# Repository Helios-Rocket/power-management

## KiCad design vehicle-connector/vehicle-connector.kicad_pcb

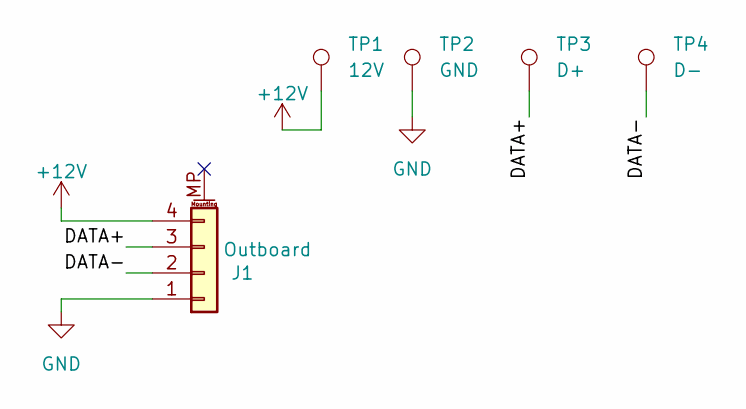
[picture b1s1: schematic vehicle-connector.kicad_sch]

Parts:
J1: Outboard; JST_ZE_SM04B-ZESS-TB_1x04-1MP_P1.50mm_Horizontal
TP1: 12V; TestPoint_Pad_4.0x4.0mm
TP2: GND; TestPoint_Pad_4.0x4.0mm
TP3: D+; TestPoint_Pad_4.0x4.0mm
TP4: D-; TestPoint_Pad_4.0x4.0mm

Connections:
+12V: J1.4, TP1.1 (1_1)
/DATA+: J1.3, TP3.1 (1_1)
/DATA-: J1.2, TP4.1 (1_1)
GND: J1.1, TP2.1 (1_1)

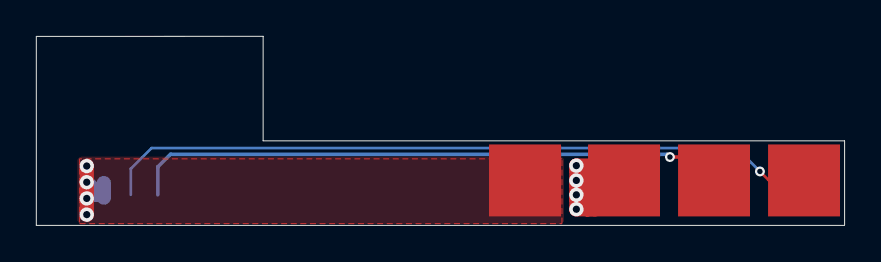
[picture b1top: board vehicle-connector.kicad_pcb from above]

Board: 2 copper layers, 44.9 x 10.5 mm, 5 parts (1 on the bottom side), 4 nets.

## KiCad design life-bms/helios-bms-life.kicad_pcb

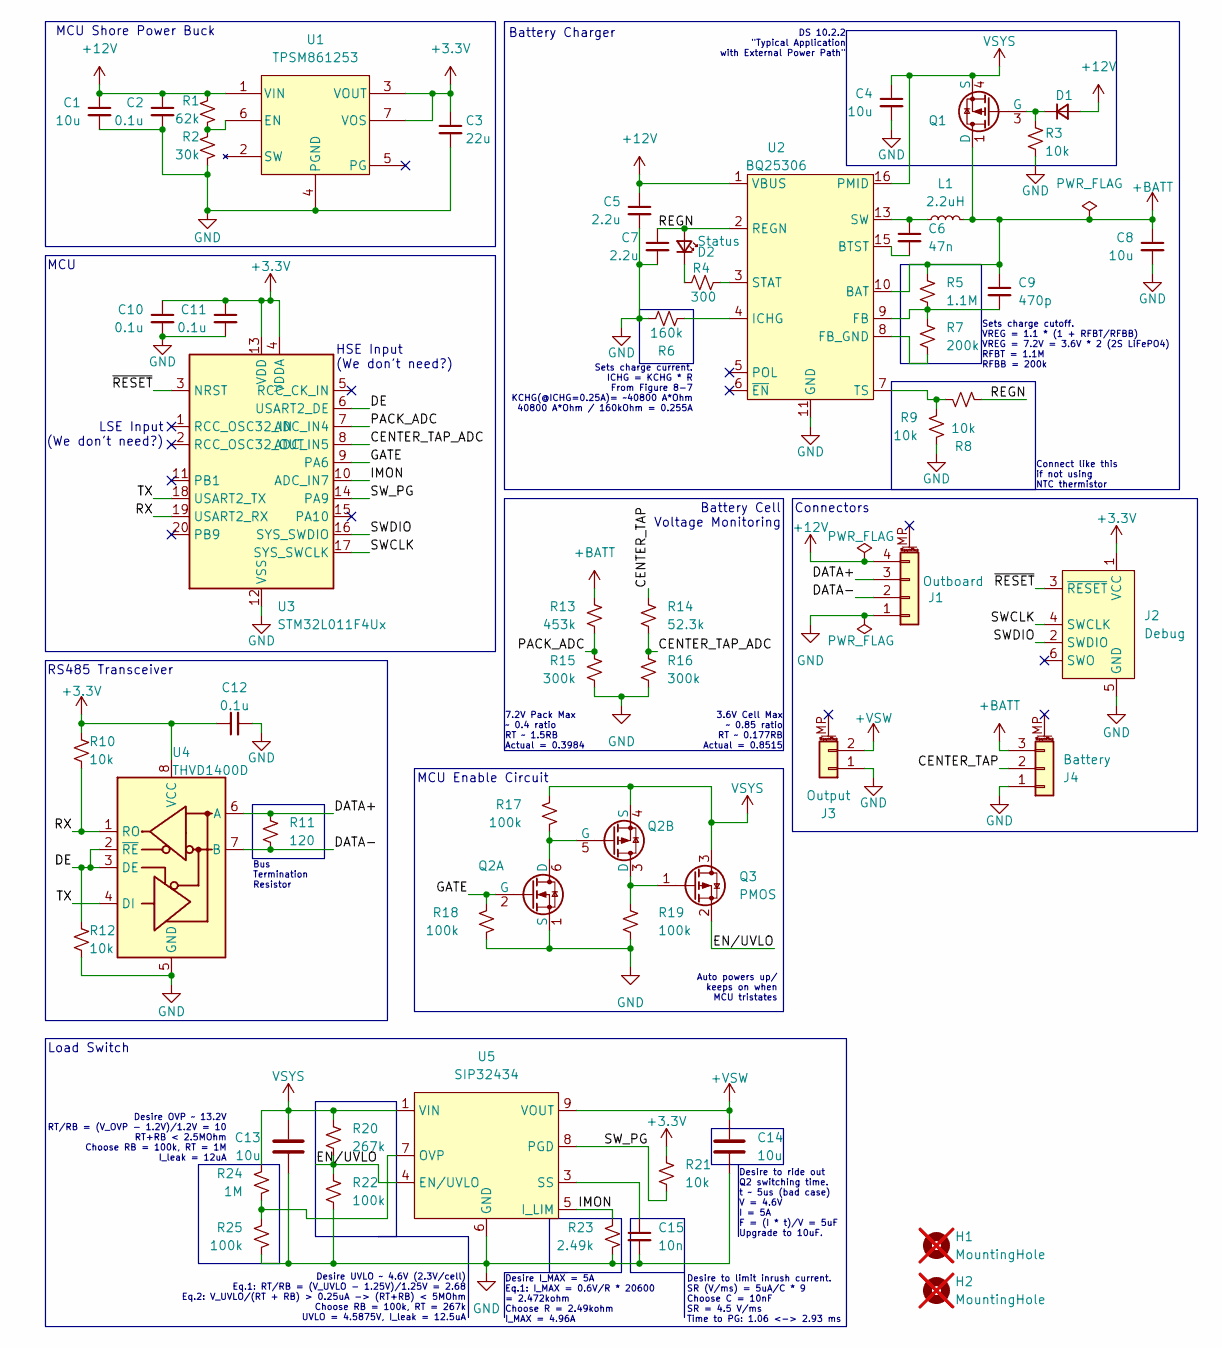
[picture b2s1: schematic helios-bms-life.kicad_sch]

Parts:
C1, C4, C8, C13, C14: 10u; C_0603_1608Metric
C2, C10, C11, C12: 0.1u; C_0402_1005Metric
C3: 22u; C_0603_1608Metric
C5, C7: 2.2u; C_0402_1005Metric
C6: 47n; C_0402_1005Metric
C9: 470p; C_0402_1005Metric
C15: 10n; C_0402_1005Metric
D1: GSDH3005; D_0402_1005Metric
D2: Status; LED_0402_1005Metric
H1, H2: MountingHole; MountingHole_3.2mm_M3_DIN965; not fitted
J1: Outboard; JST_ZE_SM04B-ZESS-TB_1x04-1MP_P1.50mm_Horizontal
J2: Debug; Tag-Connect_TC2030-IDC-NL_2x03_P1.27mm_Vertical
J3: Output; JST_ZE_SM02B-ZESS-TB_1x02-1MP_P1.50mm_Horizontal
J4: Battery; JST_ZE_SM03B-ZESS-TB_1x03-1MP_P1.50mm_Horizontal
L1: 2.2uH; L_0805_2012Metric
Q1: SSM6J507NU; SOT-1220_UDFN6B_TOS-L
Q2: Q_Dual_NMOS_PMOS_S1G1D2S2G2D1; SOT-666
Q3: PMOS; SOT-723
R1: 62k; R_0402_1005Metric
R2: 30k; R_0402_1005Metric
R3, R8, R9, R10, R12, R21: 10k; R_0402_1005Metric
R4: 300; R_0402_1005Metric
R5: 1.1M; R_0402_1005Metric
R6: 160k; R_0402_1005Metric
R7: 200k; R_0402_1005Metric
R11: 120; R_0402_1005Metric
R13: 453k; R_0402_1005Metric
R14: 52.3k; R_0402_1005Metric
R15, R16: 300k; R_0402_1005Metric
R17, R18, R19, R22, R25: 100k; R_0402_1005Metric
R20: 267k; R_0402_1005Metric
R23: 2.49k; R_0402_1005Metric
R24: 1M; R_0402_1005Metric
U1: TPSM861253; Texas-QFN-FCMOD-7_4x3.3mm
U2: BQ25306; WQFN-16-1EP_3x3mm_P0.5mm_EP1.68x1.68mm_ThermalVias
U3: STM32L011F4Ux; ST_UFQFPN-20_3x3mm_P0.5mm
U4: THVD1400D; SOT-583-8
U5: SIP32434; Maxim_TDFN-10-1EP_3x3mm_P0.5mm_EP1.58x2.35mm

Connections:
+3.3V: C3.1, C10.1, C11.1, C12.1, J2.1 (VCC), R10.1, R21.2, U1.3 (VOUT), U1.7 (VOS), U3.4 (VDDA), U3.13 (VDD), U4.8 (VCC)
+12V: C1.1, C2.1, C5.1, D1.2 (A), J1.4, R1.1, U1.1 (VIN), U2.1 (VBUS)
+BATT: C8.1, C9.1, J4.3, L1.2, Q1.1 (D), Q1.2 (D), Q1.5 (D), Q1.6 (D), Q1.7 (D), R5.1, R13.1, U2.10 (BAT)
+VSW: C14.1, J3.2, U5.9 (VOUT), U5.10 (VOUT)
/CENTER_TAP: J4.2, R14.1
/CENTER_TAP_ADC: R14.2, R16.1, U3.8 (ADC_IN5)
/DATA+: J1.3, R11.1, U4.6 (A)
/DATA-: J1.2, R11.2, U4.7 (B)
/DE: R12.1, U3.6 (USART2_DE), U4.2 (~RE), U4.3 (DE)
/EN/UVLO: Q3.2 (S), R20.1, R22.2, U5.4 (EN/UVLO)
/GATE: Q2.2 (G), R18.1, U3.9 (PA6)
/IMON: R23.2, U3.10 (ADC_IN7), U5.5 (I_LIM)
/PACK_ADC: R13.2, R15.1, U3.7 (ADC_IN4)
/REGN: C7.1, D2.2 (A), R8.2, U2.2 (REGN)
/RX: R10.2, U3.19 (USART2_RX), U4.1 (RO)
/SWCLK: J2.4 (SWCLK), U3.17 (SYS_SWCLK)
/SWDIO: J2.2 (SWDIO), U3.16 (SYS_SWDIO)
/SW_PG: R21.1, U3.14 (PA9), U5.8 (PGD)
/TX: U3.18 (USART2_TX), U4.4 (DI)
/~RESET: J2.3 (~RESET), U3.3 (NRST)
GND: C1.2, C2.2, C3.2, C4.2, C5.2, C7.2, C8.2, C10.2, C11.2, C12.2, C13.2, C14.2, C15.2, J1.1, J2.5 (GND), J3.1, J4.1, Q2.1 (S), R2.2, R3.2, R6.2, R9.2, R12.2, R15.2, R16.2, R18.2, R19.2, R22.1, R23.1, R25.1, U1.4 (PGND), U2.11 (GND), U2.12 (GND), U2.17 (GND), U3.12 (VSS), U4.5 (GND), U5.6 (GND), U5.11 (GND)
unnamed: C6.1, L1.1, U2.13 (SW), U2.14 (SW)
unnamed: D1.1 (K), Q1.3 (G), R3.1
unnamed: D2.1 (K), R4.1
unnamed: Q2.5 (G), Q2.6 (D), R17.2
unnamed: Q2.3 (D), Q3.1 (G), R19.1
unnamed: R1.2, R2.1, U1.6 (EN)
unnamed: C6.2, U2.15 (BTST)
unnamed: C9.2, R5.2, R7.1, U2.9 (FB)
unnamed: R7.2, U2.8 (FB_GND)
unnamed: R6.1, U2.4 (ICHG)
unnamed: R4.2, U2.3 (STAT)
unnamed: R8.1, R9.1, U2.7 (TS)
unnamed: R24.1, R25.2, U5.7 (OVP)
unnamed: C15.1, U5.3 (SS)
VSYS: C4.1, C13.1, Q1.4 (S), Q1.8 (S), Q2.4 (S), Q3.3 (D), R17.1, R20.2, R24.2, U2.16 (PMID), U5.1 (VIN), U5.2 (VIN)

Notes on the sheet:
LSE Input (We don't need?)
MCU Shore Power Buck
Load Switch
DS 10.2.2 "Typical Application with External Power Path"
Sets charge cutoff. VREG = 1.1 * (1 + RFBT/RFBB) VREG = 7.2V = 3.6V * 2 (2S LiFePO4) RFBT = 1.1M RFBB = 200k
Sets charge current. ICHG = KCHG * R From Figure 8-7 KCHG(@ICHG=0.25A)= ~40800 A*Ohm 40800 A*Ohm / 160kOhm = 0.255A
Connect like this if not using NTC thermistor
HSE Input (We don't need?)
RS485 Transceiver
MCU Enable Circuit
Auto powers up/ keeps on when MCU tristates
MCU
Bus Termination Resistor
Desire to limit inrush current. SR (V/ms) = 5uA/C * 9 Choose C = 10nF SR = 4.5 V/ms Time to PG: 1.06 <-> 2.93 ms
Desire UVLO ~ 4.6V (2.3V/cell) Eq.1: RT/RB = (V_UVLO - 1.25V)/1.25V = 2.68 Eq.2: V_UVLO/(RT + RB) > 0.25uA -> (RT+RB) < 5MOhm Choose RB = 100k, RT = 267k UVLO = 4.5875V, I_leak = 12.5uA
Battery Cell Voltage Monitoring
7.2V Pack Max ~ 0.4 ratio RT ~ 1.5RB Actual = 0.3984
Battery Charger
Desire I_MAX = 5A Eq.1: I_MAX = 0.6V/R * 20600 = 2.472kohm Choose R = 2.49kohm I_MAX = 4.96A
Desire OVP ~ 13.2V RT/RB = (V_OVP - 1.2V)/1.2V = 10 RT+RB < 2.5MOhm Choose RB = 100k, RT = 1M I_leak = 12uA
Desire to ride out Q2 switching time. t ~ 5us (bad case) V = 4.6V I = 5A F = (I * t)/V = 5uF Upgrade to 10uF.
3.6V Cell Max ~ 0.85 ratio RT ~ 0.177RB Actual = 0.8515
Connectors

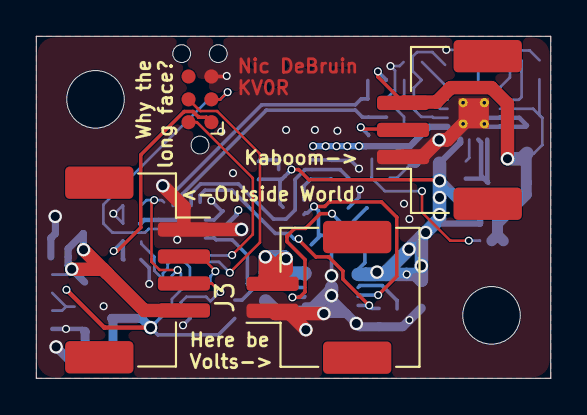
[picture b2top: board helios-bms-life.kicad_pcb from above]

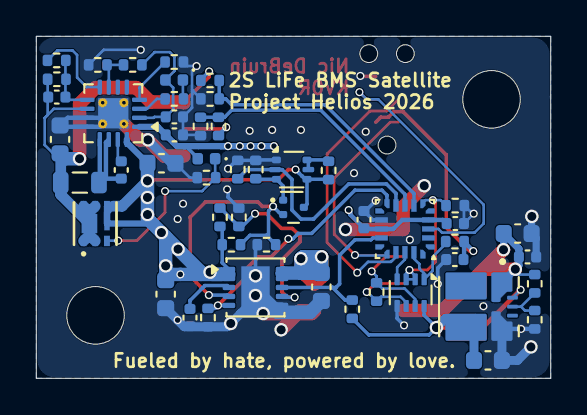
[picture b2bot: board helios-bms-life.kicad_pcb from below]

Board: 4 copper layers, 28.6 x 19.0 mm, 57 parts (51 on the bottom side), 36 nets.

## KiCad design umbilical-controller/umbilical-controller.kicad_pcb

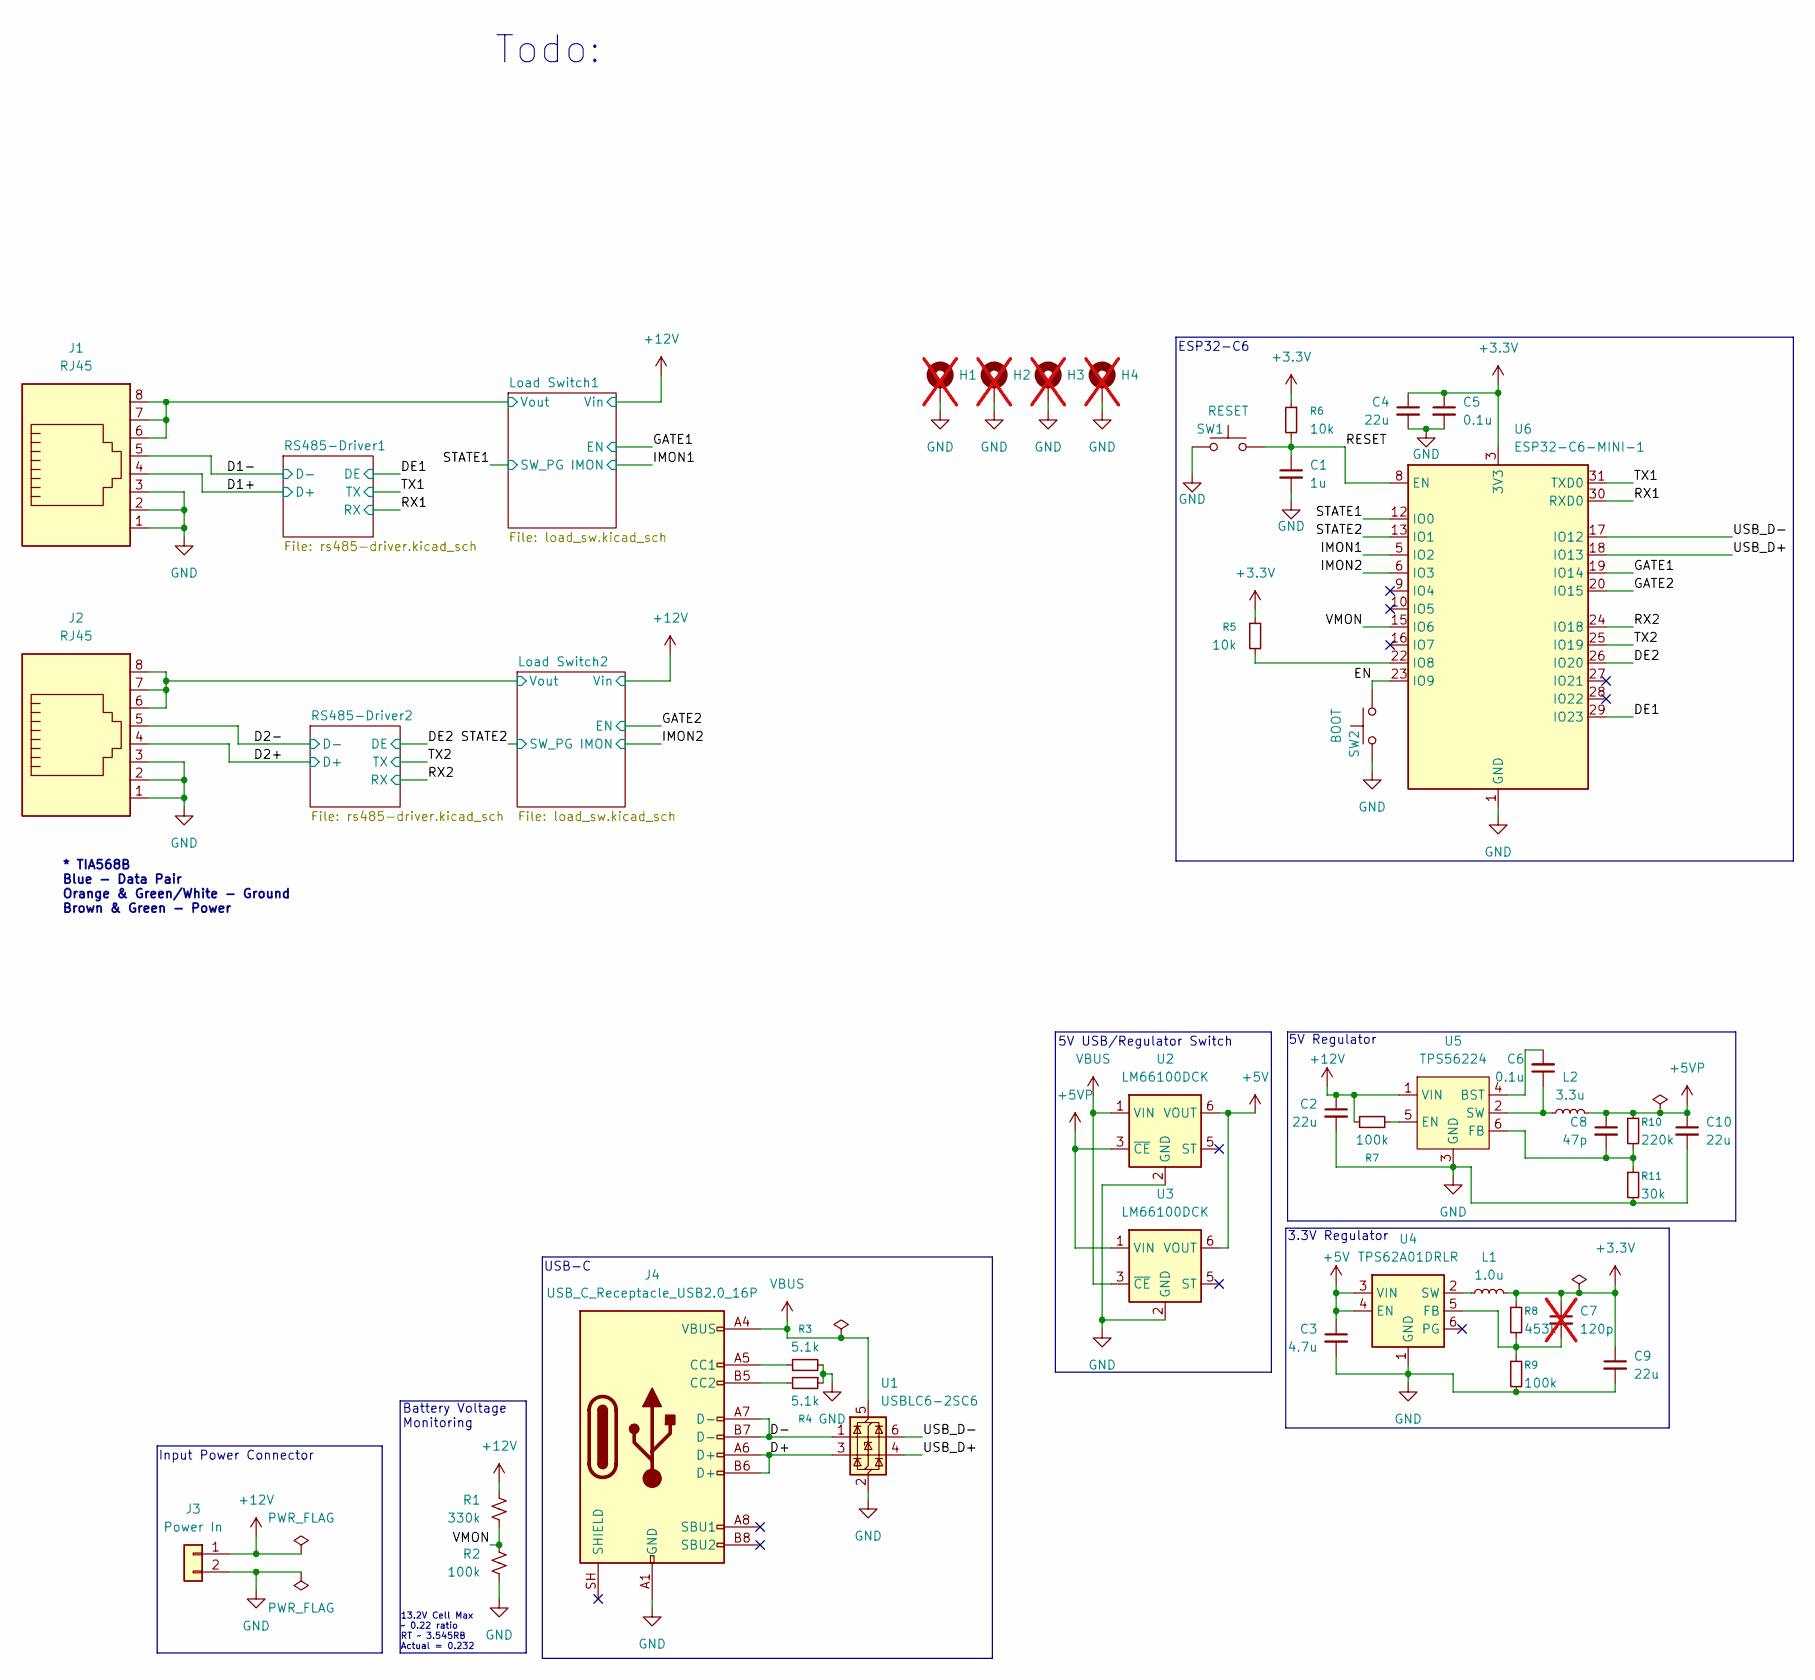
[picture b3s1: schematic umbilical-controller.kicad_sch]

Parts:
C1: 1u; C_0603_1608Metric
C2: 22u; C_0805_2012Metric
C3: 4.7u; C_0603_1608Metric
C4, C9, C10: 22u; C_0603_1608Metric
C5, C6: 0.1u; C_0603_1608Metric
C7: 120p; C_0603_1608Metric; not fitted
C8: 47p; C_0603_1608Metric
H1, H2, H3, H4: MountingHole_Pad_MP; MountingHole_4.3mm_M4_ISO7380_Pad_TopBottom; not fitted
J1, J2: RJ45; RJ45_Amphenol_54602-x08_Horizontal
J3: Power In; TerminalBlock_WAGO_2601-1102_1x02_P3.50mm_Horizontal
J4: USB_C_Receptacle_USB2.0_16P; USB_C_Receptacle_GCT_USB4105-xx-A_16P_TopMnt_Horizontal
L1: 1.0u; L_1008_2520Metric
L2: 3.3u; L_1008_2520Metric
R1: 330k; R_0603_1608Metric
R2, R7, R9: 100k; R_0603_1608Metric
R3, R4: 5.1k; R_0603_1608Metric
R5, R6: 10k; R_0603_1608Metric
R8: 453k; R_0603_1608Metric
R10: 220k; R_0603_1608Metric
R11: 30k; R_0603_1608Metric
SW1: RESET; SW_Push_1P1T_NO_E-Switch_TL3301NxxxxxG
SW2: BOOT; SW_Push_1P1T_NO_E-Switch_TL3301NxxxxxG
U1: USBLC6-2SC6; SOT-23-6
U2, U3: LM66100DCK; SOT-363_SC-70-6
U4: TPS62A01DRLR; SOT-563
U5: TPS56224; SOT-563
U6: ESP32-C6-MINI-1

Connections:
+3.3V: C4.1, C5.1, C7.1, C9.1, L1.2, R5.1, R6.1, R8.1, U6.3 (3V3); also elsewhere on the board
+5V: C3.1, U2.6 (VOUT), U3.6 (VOUT), U4.3 (VIN), U4.4 (EN)
+5VP: C8.1, C10.1, L2.2, R10.1, U2.3 (~CE), U3.1 (VIN)
+12V: C2.1, J3.1, R1.1, R7.1, U5.1 (VIN); also elsewhere on the board
/D1+: J1.4; also elsewhere on the board
/D1-: J1.5; also elsewhere on the board
/D2+: J2.4; also elsewhere on the board
/D2-: J2.5; also elsewhere on the board
/D+: J4.A6 (D+), J4.B6 (D+), U1.3 (I/O2)
/D-: J4.A7 (D-), J4.B7 (D-), U1.1 (I/O1)
/DE1: U6.29 (IO23); also elsewhere on the board
/DE2: U6.26 (IO20); also elsewhere on the board
/EN: SW2.1, U6.23 (IO9)
/GATE1: U6.19 (IO14); also elsewhere on the board
/GATE2: U6.20 (IO15); also elsewhere on the board
/IMON1: U6.5 (IO2); also elsewhere on the board
/IMON2: U6.6 (IO3); also elsewhere on the board
/Load Switch1/Vout: J1.6, J1.7, J1.8; also elsewhere on the board
/Load Switch2/Vout: J2.6, J2.7, J2.8; also elsewhere on the board
/RESET: C1.1, R6.2, SW1.1, U6.8 (EN)
/RX1: U6.30 (RXD0); also elsewhere on the board
/RX2: U6.24 (IO18); also elsewhere on the board
/STATE1: U6.12 (IO0); also elsewhere on the board
/STATE2: U6.13 (IO1); also elsewhere on the board
/TX1: U6.31 (TXD0); also elsewhere on the board
/TX2: U6.25 (IO19); also elsewhere on the board
/USB_D+: U1.4 (I/O2), U6.18 (IO13)
/USB_D-: U1.6 (I/O1), U6.17 (IO12)
/VMON: R1.2, R2.1, U6.15 (IO6)
GND: C1.2, C2.2, C3.2, C4.2, C5.2, C9.2, C10.2, H1.1 (1_1), H2.1 (1_1), H3.1 (1_1), H4.1 (1_1), J1.1, J1.2, J1.3, J2.1, J2.2, J2.3, J3.2, J4.A1 (GND), J4.A12 (GND), J4.B1 (GND), J4.B12 (GND), R2.2, R3.2, R4.1, R9.2, R11.2, SW1.2, SW2.2, U1.2 (GND), U2.2 (GND), U3.2 (GND), U4.1 (GND), U5.3 (GND), U6.1 (GND), U6.2 (GND), U6.11 (GND), U6.14 (GND), U6.36 (GND), U6.37 (GND), U6.38 (GND), U6.39 (GND), U6.40 (GND), U6.41 (GND), U6.42 (GND), U6.43 (GND), U6.44 (GND), U6.45 (GND), U6.46 (GND), U6.47 (GND), U6.48 (GND), U6.49 (GND), U6.50 (GND), U6.51 (GND), U6.52 (GND), U6.53 (GND); also elsewhere on the board
unnamed: J4.A5 (CC1), R3.1
unnamed: J4.B5 (CC2), R4.2
unnamed: C7.2, R8.2, R9.1, U4.5 (FB)
unnamed: L1.1, U4.2 (SW)
unnamed: C6.2, U5.4 (BST)
unnamed: R7.2, U5.5 (EN)
unnamed: C8.2, R10.2, R11.1, U5.6 (FB)
unnamed: C6.1, L2.1, U5.2 (SW)
unnamed: R5.2, U6.22 (IO8)
VBUS: J4.A4 (VBUS), J4.A9 (VBUS), J4.B4 (VBUS), J4.B9 (VBUS), U1.5 (VBUS), U2.1 (VIN), U3.3 (~CE)

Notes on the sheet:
Todo:
5V Regulator
3.3V Regulator
Input Power Connector
Battery Voltage Monitoring
USB-C
13.2V Cell Max ~ 0.22 ratio RT ~ 3.545RB Actual = 0.232
ESP32-C6
5V USB/Regulator Switch
* TIA568B Blue - Data Pair Orange & Green/White - Ground Brown & Green - Power

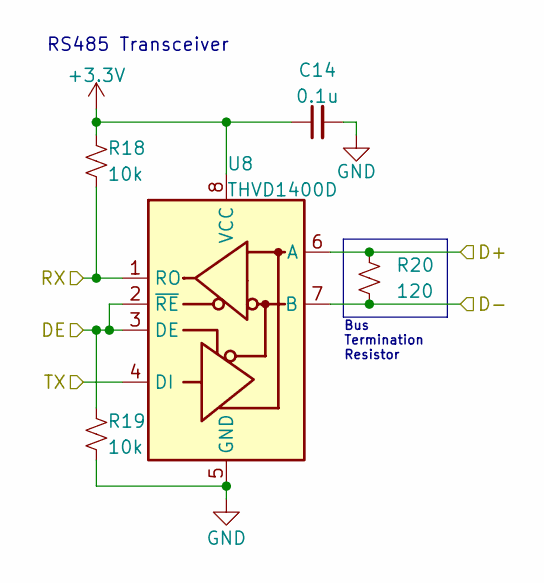
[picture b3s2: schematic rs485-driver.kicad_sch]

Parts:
C14: 0.1u; C_0603_1608Metric
R18, R19: 10k; R_0603_1608Metric
R20: 120; R_0603_1608Metric
U8: THVD1400D; SOT-583-8

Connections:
+3.3V: C14.1, R18.1, U8.8 (VCC); also elsewhere on the board
/D1+: R20.1, U8.6 (A); also elsewhere on the board
/D1-: R20.2, U8.7 (B); also elsewhere on the board
/DE1: R19.1, U8.2 (~RE), U8.3 (DE); also elsewhere on the board
/RX1: R18.2, U8.1 (RO); also elsewhere on the board
/TX1: U8.4 (DI); also elsewhere on the board
GND: C14.2, R19.2, U8.5 (GND); also elsewhere on the board

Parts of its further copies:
C15: 0.1u; C_0603_1608Metric
R21, R22: 10k; R_0603_1608Metric
R23: 120; R_0603_1608Metric
U9: THVD1400D; SOT-583-8

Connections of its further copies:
+3.3V: C15.1, R21.1, U9.8 (VCC); also elsewhere on the board
/D2+: R23.1, U9.6 (A); also elsewhere on the board
/D2-: R23.2, U9.7 (B); also elsewhere on the board
/DE2: R22.1, U9.2 (~RE), U9.3 (DE); also elsewhere on the board
/RX2: R21.2, U9.1 (RO); also elsewhere on the board
/TX2: U9.4 (DI); also elsewhere on the board
GND: C15.2, R22.2, U9.5 (GND); also elsewhere on the board

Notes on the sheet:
RS485 Transceiver
Bus Termination Resistor

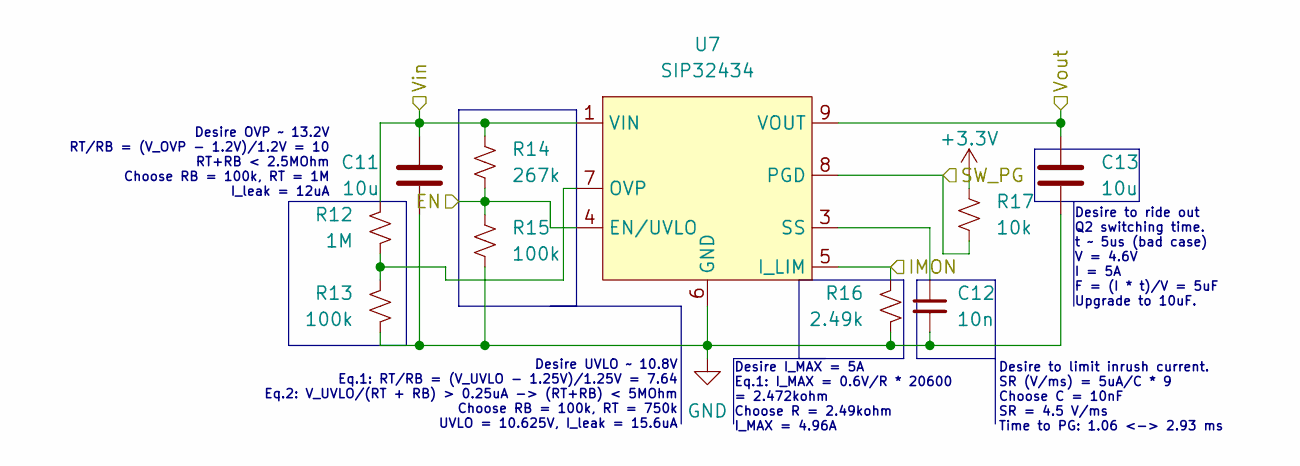
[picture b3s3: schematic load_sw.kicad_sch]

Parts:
C11, C13: 10u; C_0603_1608Metric
C12: 10n; C_0603_1608Metric
R12: 1M; R_0603_1608Metric
R13, R15: 100k; R_0603_1608Metric
R14: 267k; R_0603_1608Metric
R16: 2.49k; R_0603_1608Metric
R17: 10k; R_0603_1608Metric
U7: SIP32434; Maxim_TDFN-10-1EP_3x3mm_P0.5mm_EP1.58x2.35mm

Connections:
+3.3V: R17.2; also elsewhere on the board
+12V: C11.1, R12.2, R14.2, U7.1 (VIN), U7.2 (VIN); also elsewhere on the board
/GATE2: R14.1, R15.2, U7.4 (EN/UVLO); also elsewhere on the board
/IMON2: R16.2, U7.5 (I_LIM); also elsewhere on the board
/Load Switch2/Vout: C13.1, U7.9 (VOUT), U7.10 (VOUT); also elsewhere on the board
/STATE2: R17.1, U7.8 (PGD); also elsewhere on the board
GND: C11.2, C12.2, C13.2, R13.1, R15.1, R16.1, U7.6 (GND), U7.11 (GND); also elsewhere on the board
unnamed: R12.1, R13.2, U7.7 (OVP)
unnamed: C12.1, U7.3 (SS)

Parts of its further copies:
C16, C18: 10u; C_0603_1608Metric
C17: 10n; C_0603_1608Metric
R24: 1M; R_0603_1608Metric
R25, R27: 100k; R_0603_1608Metric
R26: 267k; R_0603_1608Metric
R28: 2.49k; R_0603_1608Metric
R29: 10k; R_0603_1608Metric
U10: SIP32434; Maxim_TDFN-10-1EP_3x3mm_P0.5mm_EP1.58x2.35mm

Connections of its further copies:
+3.3V: R29.2; also elsewhere on the board
+12V: C16.1, R24.2, R26.2, U10.1 (VIN), U10.2 (VIN); also elsewhere on the board
/GATE1: R26.1, R27.2, U10.4 (EN/UVLO); also elsewhere on the board
/IMON1: R28.2, U10.5 (I_LIM); also elsewhere on the board
/Load Switch1/Vout: C18.1, U10.9 (VOUT), U10.10 (VOUT); also elsewhere on the board
/STATE1: R29.1, U10.8 (PGD); also elsewhere on the board
GND: C16.2, C17.2, C18.2, R25.1, R27.1, R28.1, U10.6 (GND), U10.11 (GND); also elsewhere on the board
unnamed: R24.1, R25.2, U10.7 (OVP)
unnamed: C17.1, U10.3 (SS)

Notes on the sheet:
Desire to limit inrush current. SR (V/ms) = 5uA/C * 9 Choose C = 10nF SR = 4.5 V/ms Time to PG: 1.06 <-> 2.93 ms
Desire OVP ~ 13.2V RT/RB = (V_OVP - 1.2V)/1.2V = 10 RT+RB < 2.5MOhm Choose RB = 100k, RT = 1M I_leak = 12uA
Desire I_MAX = 5A Eq.1: I_MAX = 0.6V/R * 20600 = 2.472kohm Choose R = 2.49kohm I_MAX = 4.96A
Desire to ride out Q2 switching time. t ~ 5us (bad case) V = 4.6V I = 5A F = (I * t)/V = 5uF Upgrade to 10uF.
Desire UVLO ~ 10.8V Eq.1: RT/RB = (V_UVLO - 1.25V)/1.25V = 7.64 Eq.2: V_UVLO/(RT + RB) > 0.25uA -> (RT+RB) < 5MOhm Choose RB = 100k, RT = 750k UVLO = 10.625V, I_leak = 15.6uA

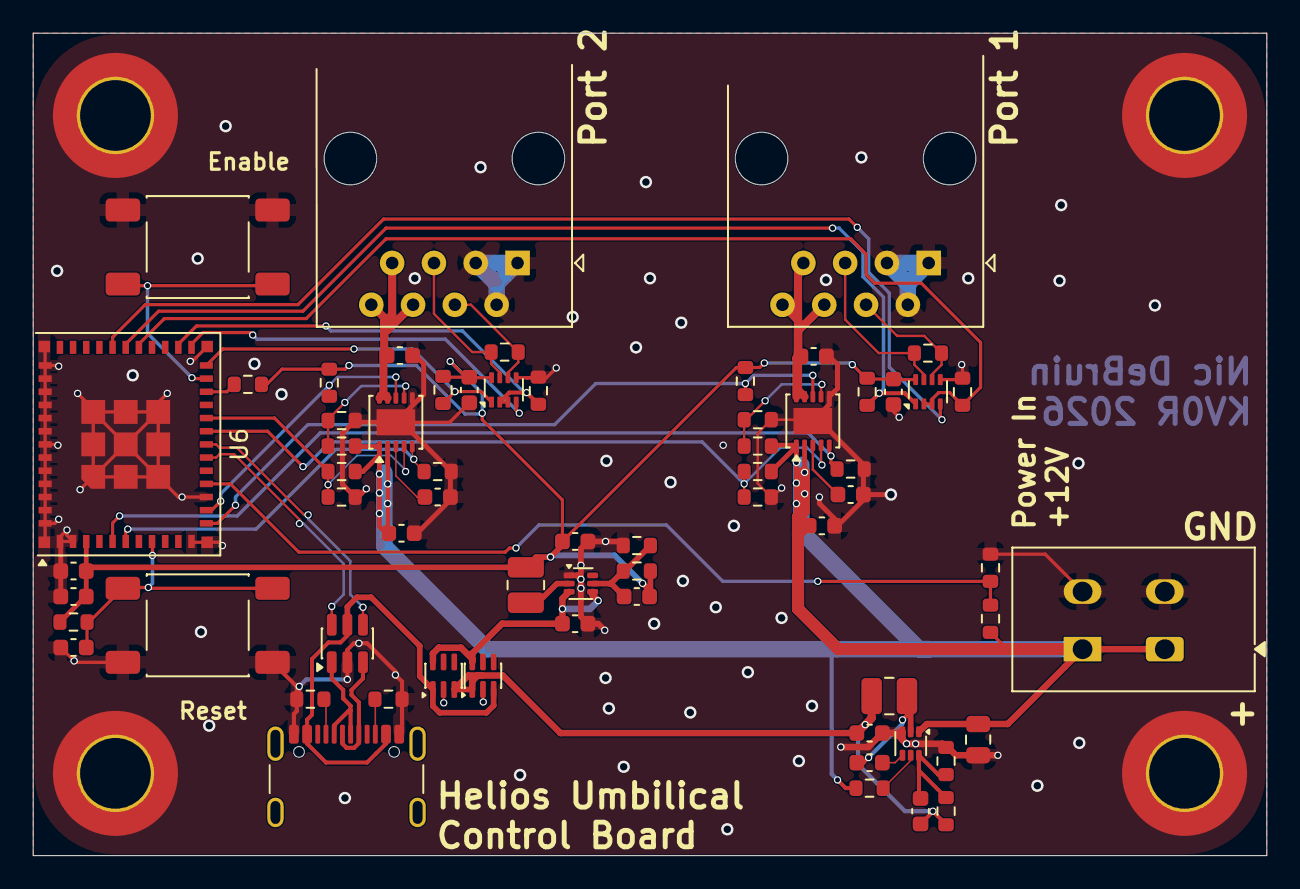
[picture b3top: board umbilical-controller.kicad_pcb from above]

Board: 2 copper layers, 75.0 x 50.0 mm, 69 parts (0 on the bottom side), 44 nets.

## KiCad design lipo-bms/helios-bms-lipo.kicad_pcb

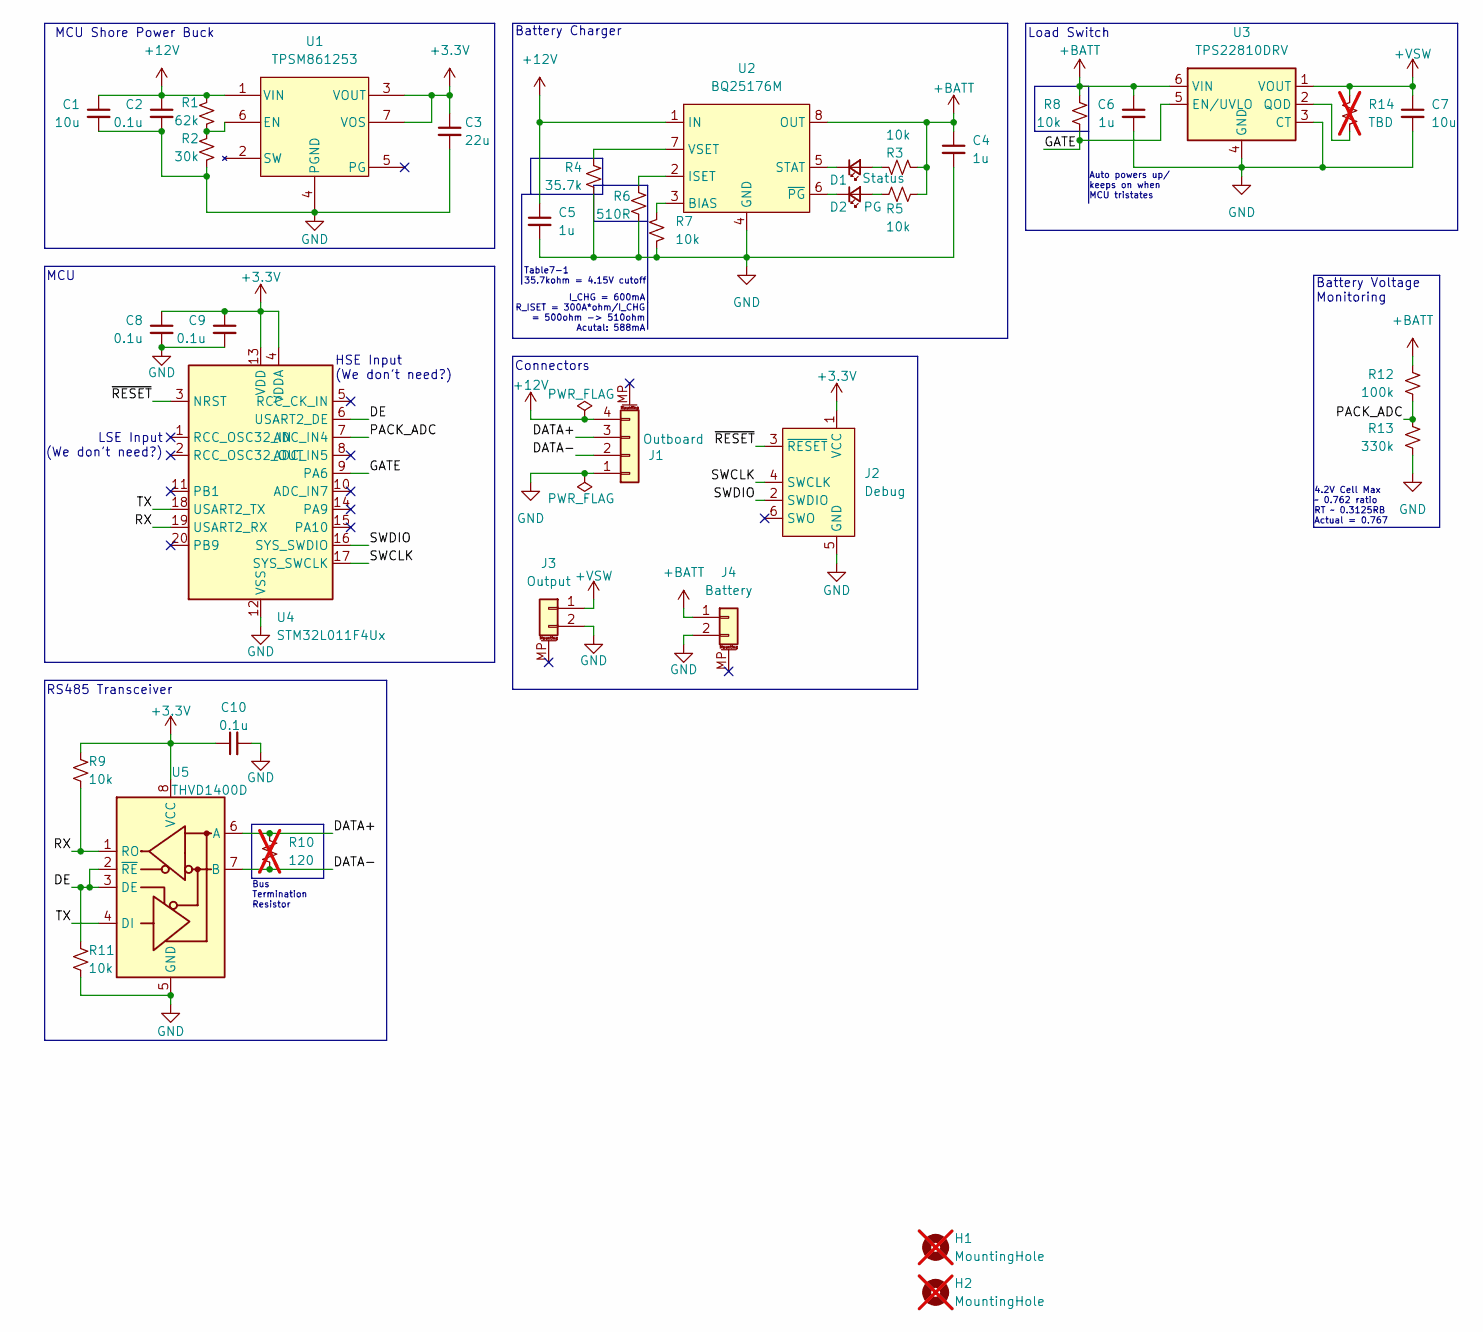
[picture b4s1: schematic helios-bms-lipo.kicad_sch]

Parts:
C1, C7: 10u; C_0603_1608Metric
C2, C8, C9, C10: 0.1u; C_0402_1005Metric
C3: 22u; C_0603_1608Metric
C4, C5, C6: 1u; C_0402_1005Metric
D1: Status; LED_0402_1005Metric
D2: PG; LED_0402_1005Metric
H1, H2: MountingHole; MountingHole_3.2mm_M3_DIN965; not fitted
J1: Outboard; JST_ZE_SM04B-ZESS-TB_1x04-1MP_P1.50mm_Horizontal
J2: Debug; Tag-Connect_TC2030-IDC-NL_2x03_P1.27mm_Vertical
J3: Output; JST_PH_S2B-PH-SM4-TB_1x02-1MP_P2.00mm_Horizontal
J4: Battery; JST_PH_S2B-PH-SM4-TB_1x02-1MP_P2.00mm_Horizontal
R1: 62k; R_0402_1005Metric
R2: 30k; R_0402_1005Metric
R3, R5, R7, R8, R9, R11: 10k; R_0402_1005Metric
R4: 35.7k; R_0402_1005Metric
R6: 510R; R_0402_1005Metric
R10: 120; R_0402_1005Metric; not fitted
R12: 100k; R_0402_1005Metric
R13: 330k; R_0402_1005Metric
R14: TBD; R_0402_1005Metric; not fitted
U1: TPSM861253; Texas-QFN-FCMOD-7_4x3.3mm
U2: BQ25176M; WSON-8-1EP_2x2mm_P0.5mm_EP0.9x1.6mm_ThermalVias
U3: TPS22810DRV; WSON-6-1EP_2x2mm_P0.65mm_EP1x1.6mm
U4: STM32L011F4Ux; ST_UFQFPN-20_3x3mm_P0.5mm
U5: THVD1400D; SOT-583-8

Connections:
+3.3V: C3.1, C8.1, C9.1, C10.1, J2.1 (VCC), R9.1, U1.3 (VOUT), U1.7 (VOS), U4.4 (VDDA), U4.13 (VDD), U5.8 (VCC)
+12V: C1.1, C2.1, C5.1, J1.4, R1.1, U1.1 (VIN), U2.1 (IN)
+BATT: C4.1, C6.1, J4.1, R3.2, R5.2, R8.1, R12.1, U2.8 (OUT), U3.6 (VIN)
+VSW: C7.1, J3.1, R14.1, U3.1 (VOUT)
/DATA+: J1.3, R10.1, U5.6 (A)
/DATA-: J1.2, R10.2, U5.7 (B)
/DE: R11.1, U4.6 (USART2_DE), U5.2 (~RE), U5.3 (DE)
/GATE: R8.2, U3.5 (EN/UVLO), U4.9 (PA6)
/PACK_ADC: R12.2, R13.1, U4.7 (ADC_IN4)
/RX: R9.2, U4.19 (USART2_RX), U5.1 (RO)
/SWCLK: J2.4 (SWCLK), U4.17 (SYS_SWCLK)
/SWDIO: J2.2 (SWDIO), U4.16 (SYS_SWDIO)
/TX: U4.18 (USART2_TX), U5.4 (DI)
/~RESET: J2.3 (~RESET), U4.3 (NRST)
GND: C1.2, C2.2, C3.2, C4.2, C5.2, C6.2, C7.2, C8.2, C9.2, C10.2, J1.1, J2.5 (GND), J3.2, J4.2, R2.2, R4.2, R6.2, R7.2, R11.2, R13.2, U1.4 (PGND), U2.4 (GND), U2.9 (GND), U3.3 (CT), U3.4 (GND), U3.7 (GND), U4.12 (VSS), U5.5 (GND)
unnamed: D1.2 (A), R3.1
unnamed: D1.1 (K), U2.5 (STAT)
unnamed: D2.2 (A), R5.1
unnamed: D2.1 (K), U2.6 (~PG)
unnamed: R1.2, R2.1, U1.6 (EN)
unnamed: R7.1, U2.3 (BIAS)
unnamed: R6.1, U2.2 (ISET)
unnamed: R4.1, U2.7 (VSET)
unnamed: R14.2, U3.2 (QOD)

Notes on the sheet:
LSE Input (We don't need?)
MCU Shore Power Buck
Battery Charger
HSE Input (We don't need?)
RS485 Transceiver
MCU
Bus Termination Resistor
Table7-1 35.7kohm = 4.15V cutoff
Battery Voltage Monitoring
Load Switch
I_CHG = 600mA R_ISET = 300A*ohm/I_CHG = 500ohm -> 510ohm Acutal: 588mA
4.2V Cell Max ~ 0.762 ratio RT ~ 0.3125RB Actual = 0.767
Auto powers up/ keeps on when MCU tristates
Connectors

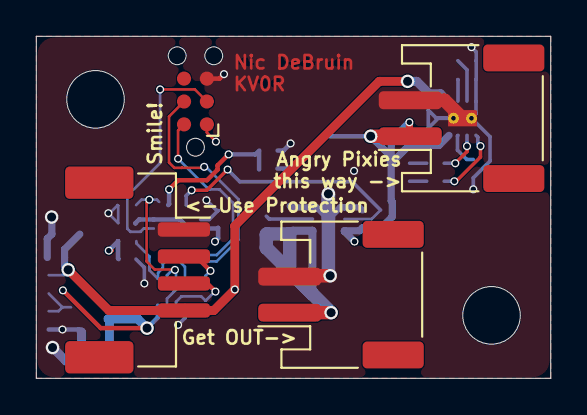
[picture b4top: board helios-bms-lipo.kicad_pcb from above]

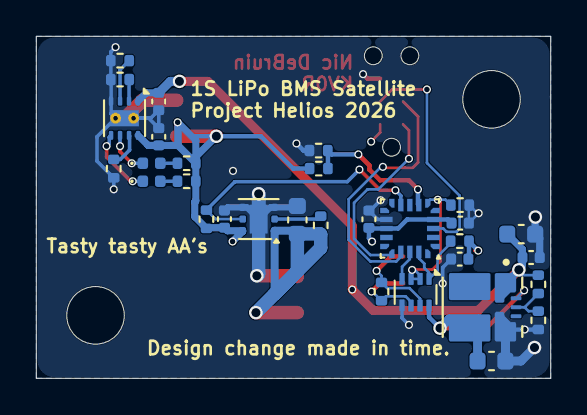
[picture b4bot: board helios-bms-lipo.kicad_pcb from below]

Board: 4 copper layers, 28.6 x 19.0 mm, 37 parts (31 on the bottom side), 24 nets.
